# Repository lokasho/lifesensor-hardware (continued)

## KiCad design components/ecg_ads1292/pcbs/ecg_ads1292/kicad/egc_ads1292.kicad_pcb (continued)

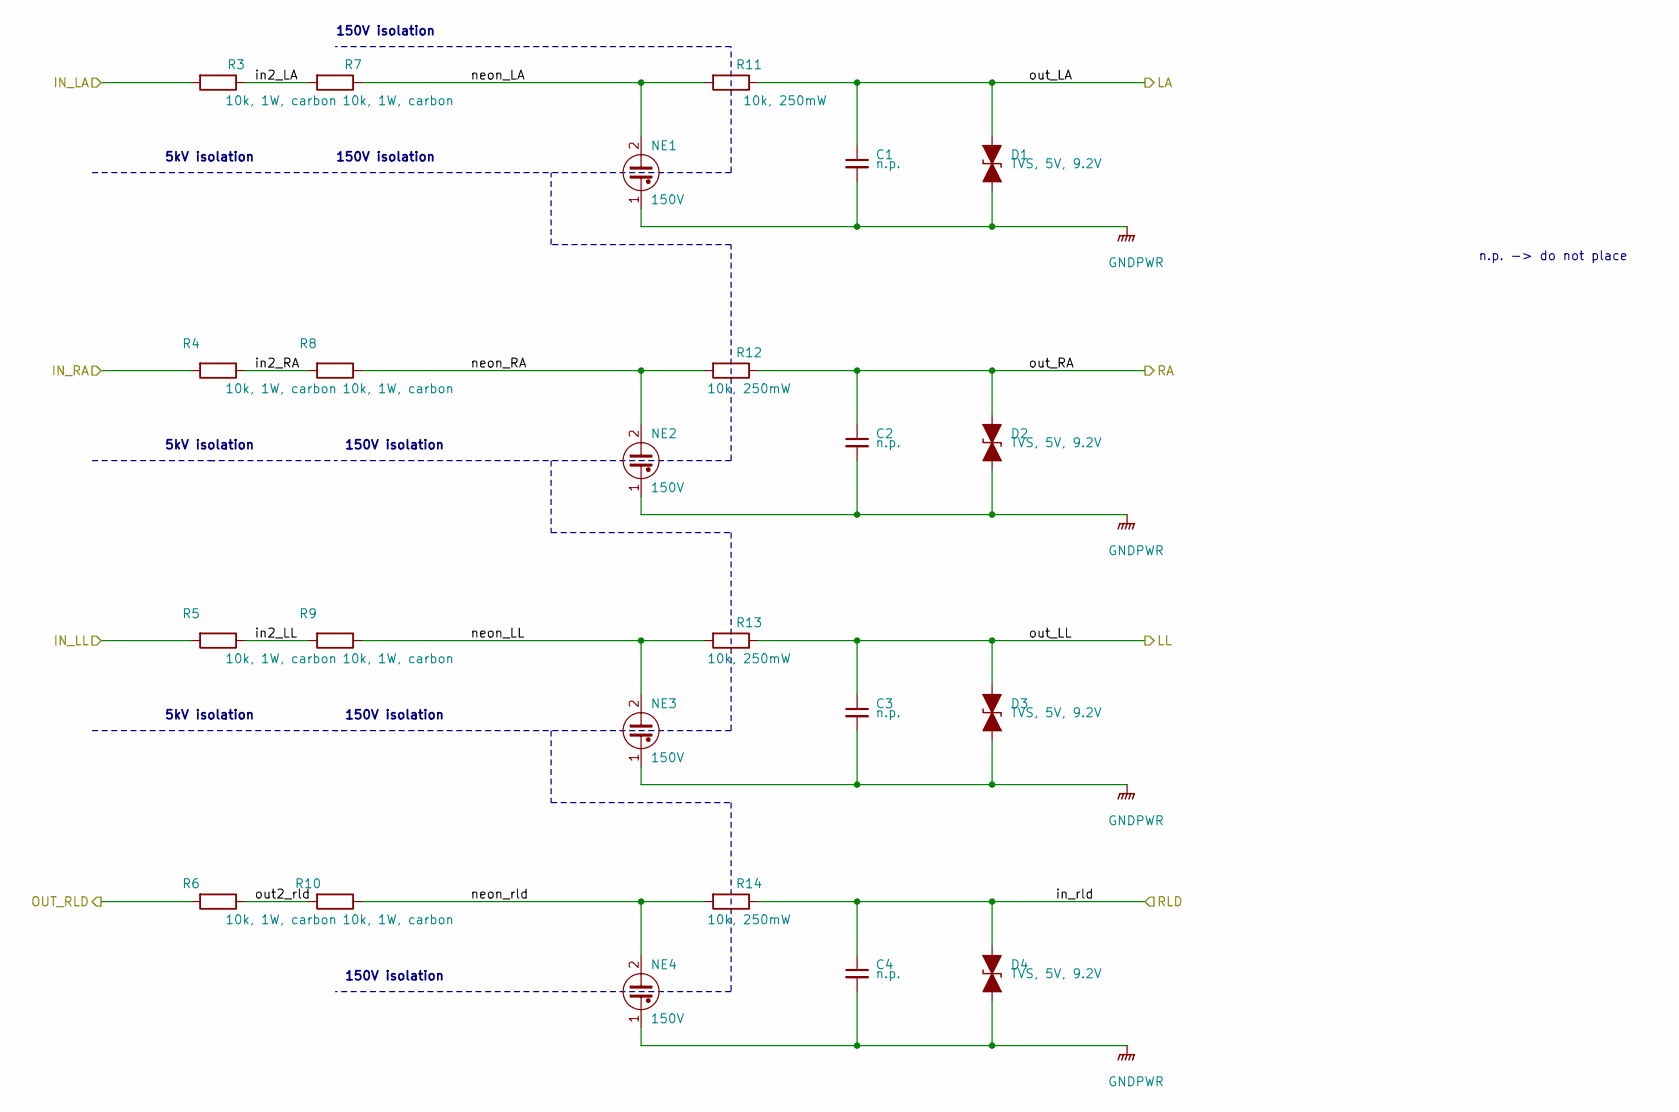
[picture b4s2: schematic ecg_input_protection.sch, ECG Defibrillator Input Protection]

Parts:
C1, C2, C3, C4: n.p.; C_Rect_L4.0mm_W2.5mm_P2.50mm
D1, D2, D3, D4: TVS, 5V, 9.2V; D_SMB_Handsoldering
NE1, NE2, NE3, NE4: 150V; C_Radial_D8.0mm_H11.5mm_P3.50mm
R3, R4, R5, R6, R7, R8, R9, R10: 10k, 1W, carbon; R_Axial_DIN0309_L9.0mm_D3.2mm_P12.70mm_Horizontal
R11, R12, R13, R14: 10k, 250mW; R_Axial_DIN0207_L6.3mm_D2.5mm_P10.16mm_Horizontal

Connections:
/ecg input protection/in2_LA: R3.1, R7.2
/ecg input protection/in2_LL: R5.1, R9.2
/ecg input protection/in2_RA: R4.1, R8.2
/ecg input protection/neon_LA: NE1.2, R7.1, R11.2
/ecg input protection/neon_LL: NE3.2, R9.1, R13.2
/ecg input protection/neon_RA: NE2.2, R8.1, R12.2
/ecg input protection/neon_rld: NE4.2, R10.1, R14.2
/ecg input protection/out2_rld: R6.1, R10.2
/in_LA: R3.2; also elsewhere on the board
/in_LL: R5.2; also elsewhere on the board
/in_RA: R4.2; also elsewhere on the board
/out_rld: R6.2; also elsewhere on the board
/protected_LA: C1.1, D1.1 (A1), R11.1; also elsewhere on the board
/protected_LL: C3.1, D3.1 (A1), R13.1; also elsewhere on the board
/protected_RA: C2.1, D2.1 (A1), R12.1; also elsewhere on the board
/protected_RLD: C4.1, D4.1 (A1), R14.1; also elsewhere on the board
GNDPWR: C1.2, C2.2, C3.2, C4.2, D1.2 (A2), D2.2 (A2), D3.2 (A2), D4.2 (A2), NE1.1, NE2.1, NE3.1, NE4.1; also elsewhere on the board

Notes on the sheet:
150V isolation
5kV isolation
n.p. -> do not place

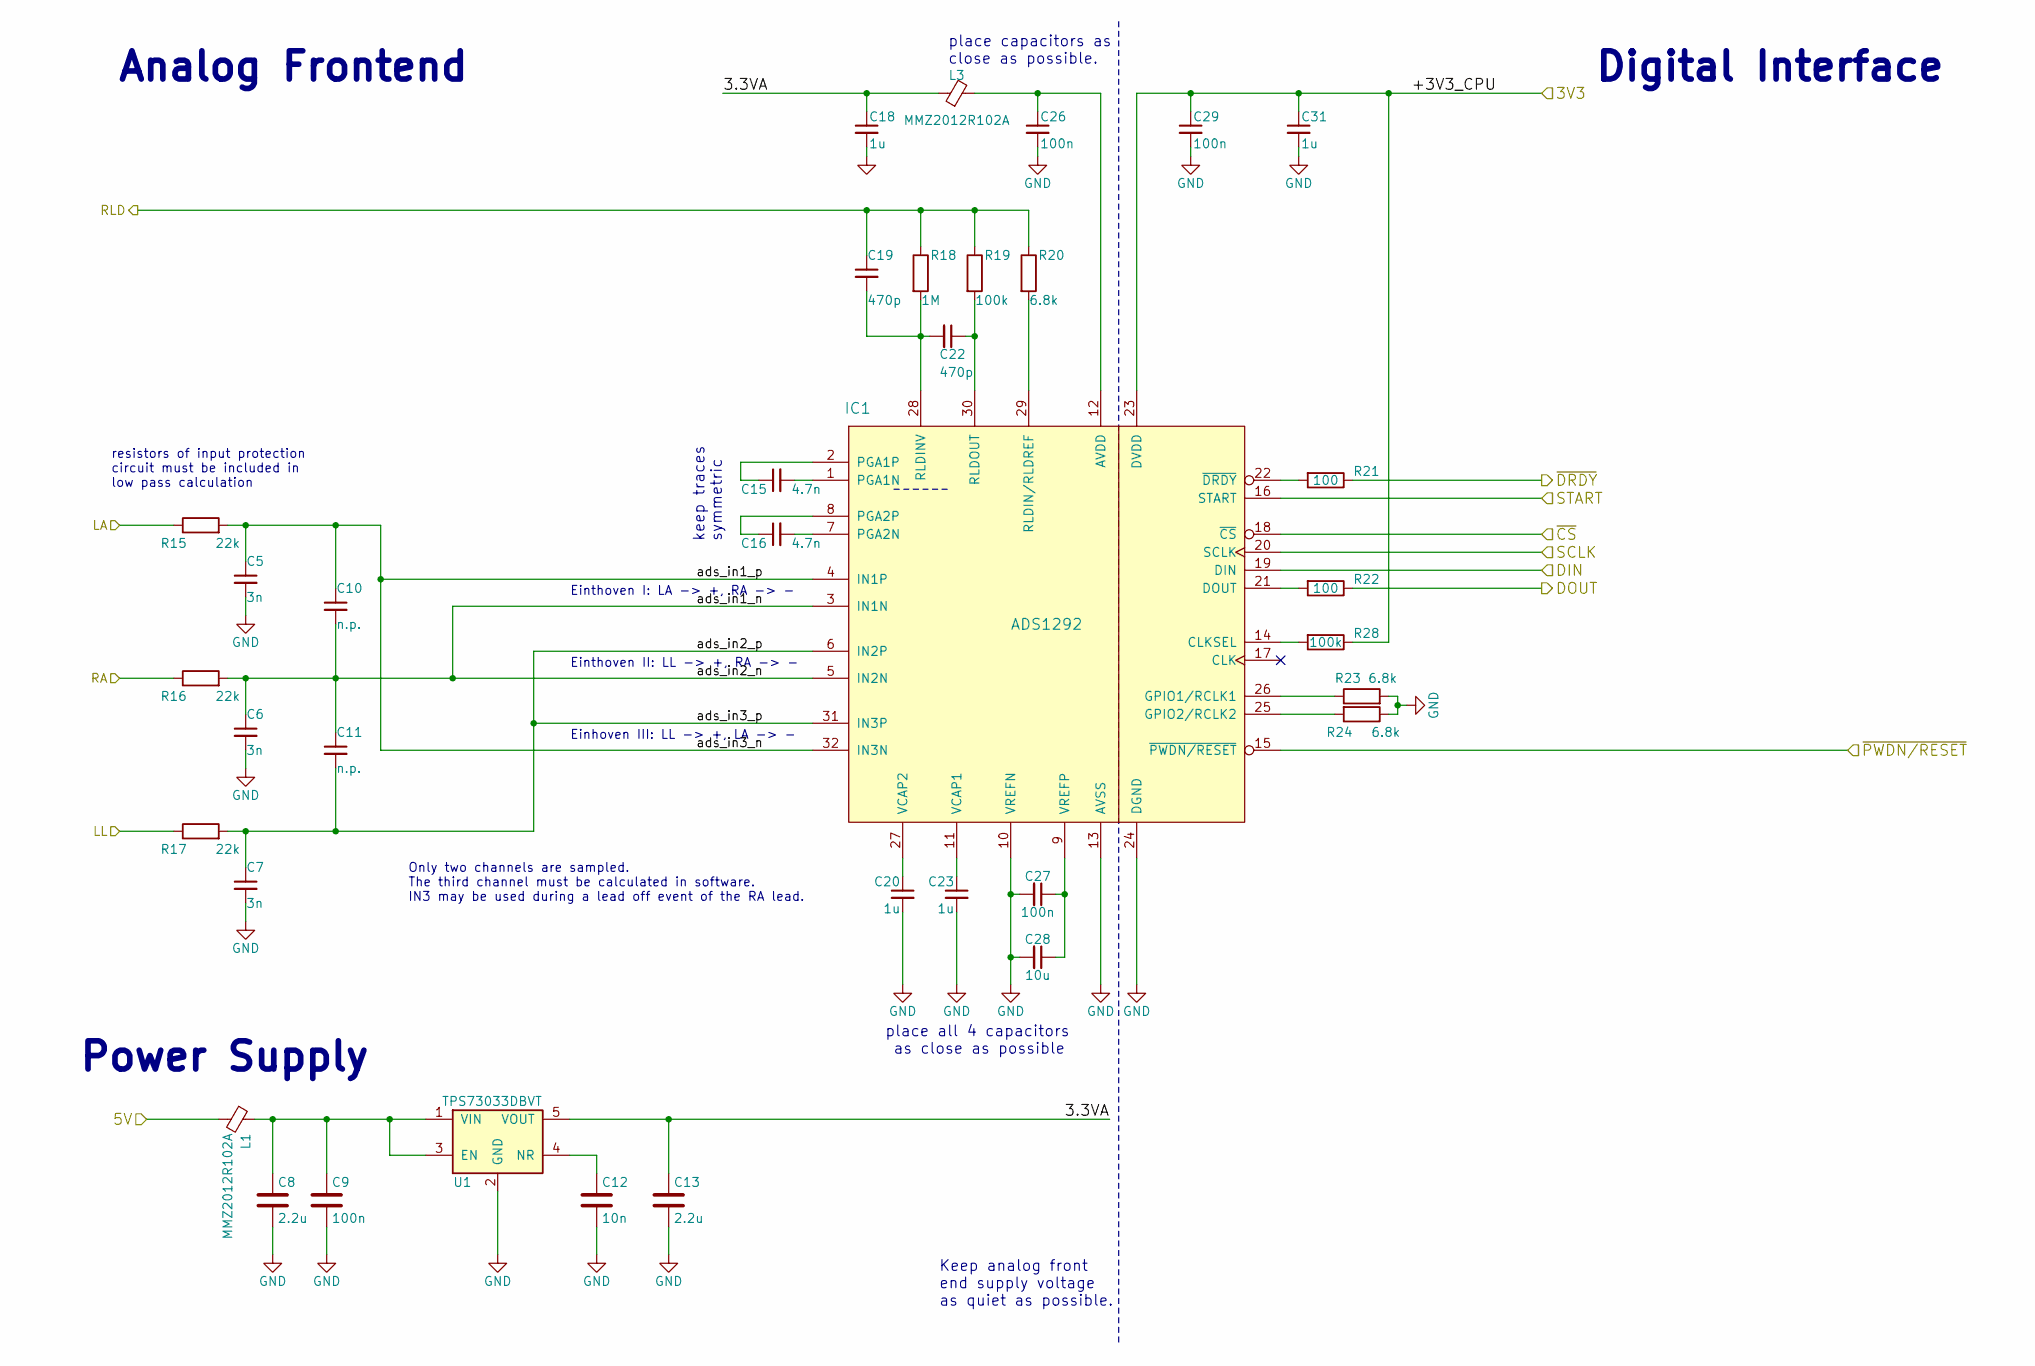
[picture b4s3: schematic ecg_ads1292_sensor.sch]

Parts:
C5, C6, C7: 3n; C_0603_1608Metric_Pad1.05x0.95mm_HandSolder; Farnell 1865491
C8, C13: 2.2u; C_0603_1608Metric_Pad1.05x0.95mm_HandSolder; Farnell 1797012
C9, C26, C29: 100n; C_0603_1608Metric_Pad1.05x0.95mm_HandSolder; Farnell 1907318
C10, C11: n.p.; C_0603_1608Metric_Pad1.05x0.95mm_HandSolder; Farnell 1865491
C12: 10n; C_0603_1608Metric_Pad1.05x0.95mm_HandSolder; Farnell 2496825
C15, C16: 4.7n; C_0603_1608Metric_Pad1.05x0.95mm_HandSolder; Farnell 2611918
C18, C20, C23, C31: 1u; C_0603_1608Metric_Pad1.05x0.95mm_HandSolder; Farnell 2112849
C19, C22: 470p; C_0603_1608Metric_Pad1.05x0.95mm_HandSolder
C27: 100n; C_0603_1608Metric_Pad1.05x0.95mm_HandSolder; Farnell 2494294
C28: 10u; C_0603_1608Metric_Pad1.05x0.95mm_HandSolder; Farnell 1889276
IC1: ADS1292; LQFP-32_5x5mm_P0.5mm
L1, L3: MMZ2012R102A; L_0805_2012Metric_Pad1.15x1.40mm_HandSolder; Farnell 1669719
R15, R16, R17: 22k; R_0603_1608Metric_Pad1.05x0.95mm_HandSolder; Farnell 1469825
R18: 1M; R_0603_1608Metric_Pad1.05x0.95mm_HandSolder; Farnell 1469746
R19: 100k; R_0603_1608Metric_Pad1.05x0.95mm_HandSolder; Farnell 1692517
R20, R23, R24: 6.8k; R_0603_1608Metric_Pad1.05x0.95mm_HandSolder; Farnell 1738916
R21, R22: 100; R_0603_1608Metric_Pad1.05x0.95mm_HandSolder; Farnell 1739145
R28: 100k; R_0603_1608Metric_Pad1.05x0.95mm_HandSolder; Farnell 1739145
U1: TPS73033DBVT; SOT-23-5_HandSoldering; Farnell 1135395

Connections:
/3V3: C29.1, C31.1, IC1.23 (DVDD), R28.1; also elsewhere on the board
/5V: L1.2; also elsewhere on the board
/ECG Sensor/3.3VA: C13.1, C18.1, L3.1, U1.5 (VOUT)
/ECG Sensor/ads_in1_n: C6.1, C10.2, C11.1, IC1.3 (IN1N), IC1.5 (IN2N), R16.2
/ECG Sensor/ads_in1_p: C5.1, C10.1, IC1.4 (IN1P), IC1.32 (IN3N), R15.2
/ECG Sensor/ads_in2_p: C7.1, C11.2, IC1.6 (IN2P), IC1.31 (IN3P), R17.2
/MISO: R22.1; also elsewhere on the board
/MOSI: IC1.19 (DIN); also elsewhere on the board
/SCLK: IC1.20 (SCLK); also elsewhere on the board
/START: IC1.16 (START); also elsewhere on the board
/protected_LA: R15.1; also elsewhere on the board
/protected_LL: R17.1; also elsewhere on the board
/protected_RA: R16.1; also elsewhere on the board
/protected_RLD: C19.1, R18.1, R19.1, R20.1; also elsewhere on the board
/~CS_ECG: IC1.18 (~CS); also elsewhere on the board
/~DRDY: R21.1; also elsewhere on the board
/~PDN_RESET: IC1.15 (~PWDN/RESET); also elsewhere on the board
GND: C5.2, C6.2, C7.2, C8.2, C9.2, C12.2, C13.2, C18.2, C20.2, C23.2, C26.2, C27.2, C28.2, C29.2, C31.2, IC1.10 (VREFN), IC1.13 (AVSS), IC1.24 (DGND), R23.2, R24.1, U1.2 (GND); also elsewhere on the board
unnamed: C8.1, C9.1, L1.1, U1.1 (VIN), U1.3 (EN)
unnamed: C12.1, U1.4 (NR)
unnamed: C15.1, IC1.2 (PGA1P)
unnamed: C15.2, IC1.1 (PGA1N)
unnamed: C16.1, IC1.8 (PGA2P)
unnamed: C16.2, IC1.7 (PGA2N)
unnamed: C19.2, C22.2, IC1.28 (RLDINV), R18.2
unnamed: C20.1, IC1.27 (VCAP2)
unnamed: C22.1, IC1.30 (RLDOUT), R19.2
unnamed: C23.1, IC1.11 (VCAP1)
unnamed: C26.1, IC1.12 (AVDD), L3.2
unnamed: C27.1, C28.1, IC1.9 (VREFP)
unnamed: IC1.14 (CLKSEL), R28.2
unnamed: IC1.21 (DOUT), R22.2
unnamed: IC1.22 (~DRDY), R21.2
unnamed: IC1.25 (GPIO2/RCLK2), R24.2
unnamed: IC1.26 (GPIO1/RCLK1), R23.1
unnamed: IC1.29 (RLDIN/RLDREF), R20.2

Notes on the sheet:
place all 4 capacitors as close as possible
Digital Interface
Analog Frontend
Keep analog front end supply voltage as quiet as possible.
place capacitors as close as possible.
keep traces symmetric
Power Supply
Einthoven I: LA -> +, RA -> -
Einthoven II: LL -> +, RA -> -
Einhoven III: LL -> +, LA -> -
resistors of input protection circuit must be included in low pass calculation
Only two channels are sampled. The third channel must be calculated in software. IN3 may be used during a lead off event of the RA lead.

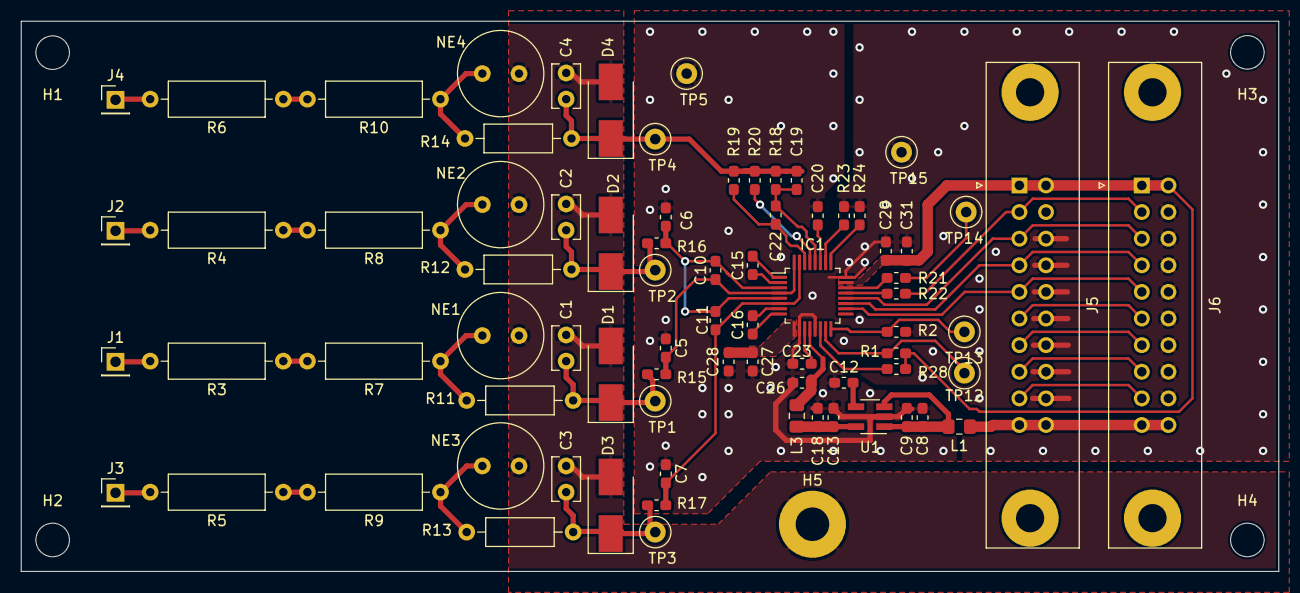
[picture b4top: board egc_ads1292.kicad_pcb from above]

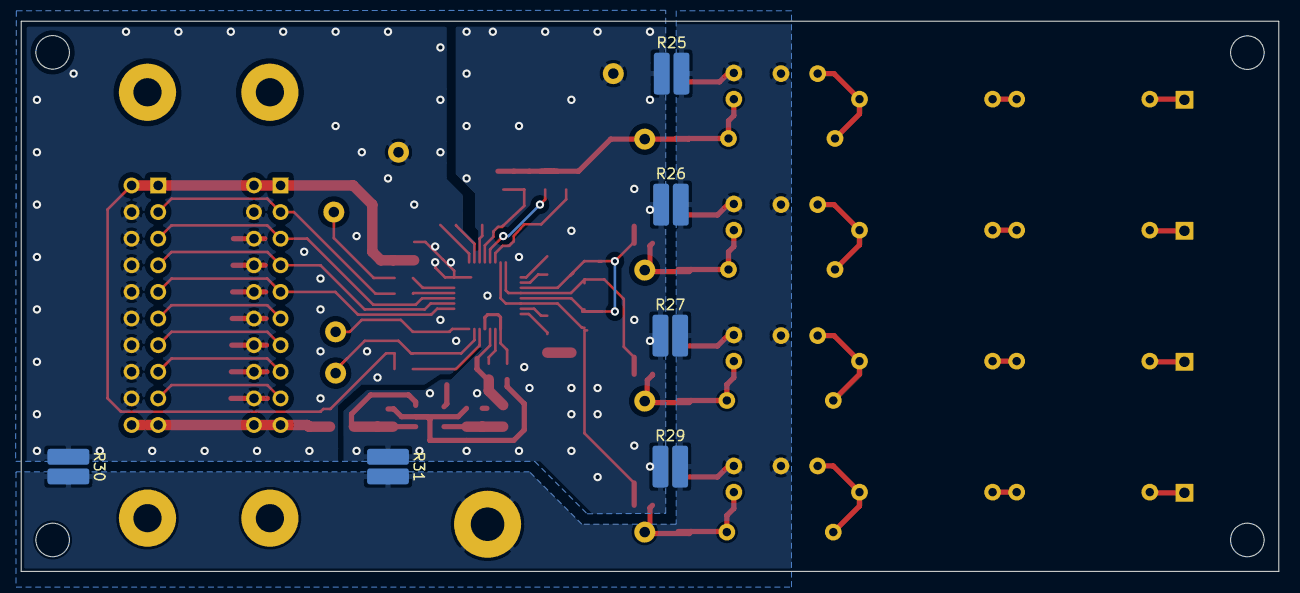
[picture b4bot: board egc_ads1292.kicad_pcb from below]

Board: 2 copper layers, 120.0 x 52.5 mm, 88 parts (6 on the bottom side), 53 nets.

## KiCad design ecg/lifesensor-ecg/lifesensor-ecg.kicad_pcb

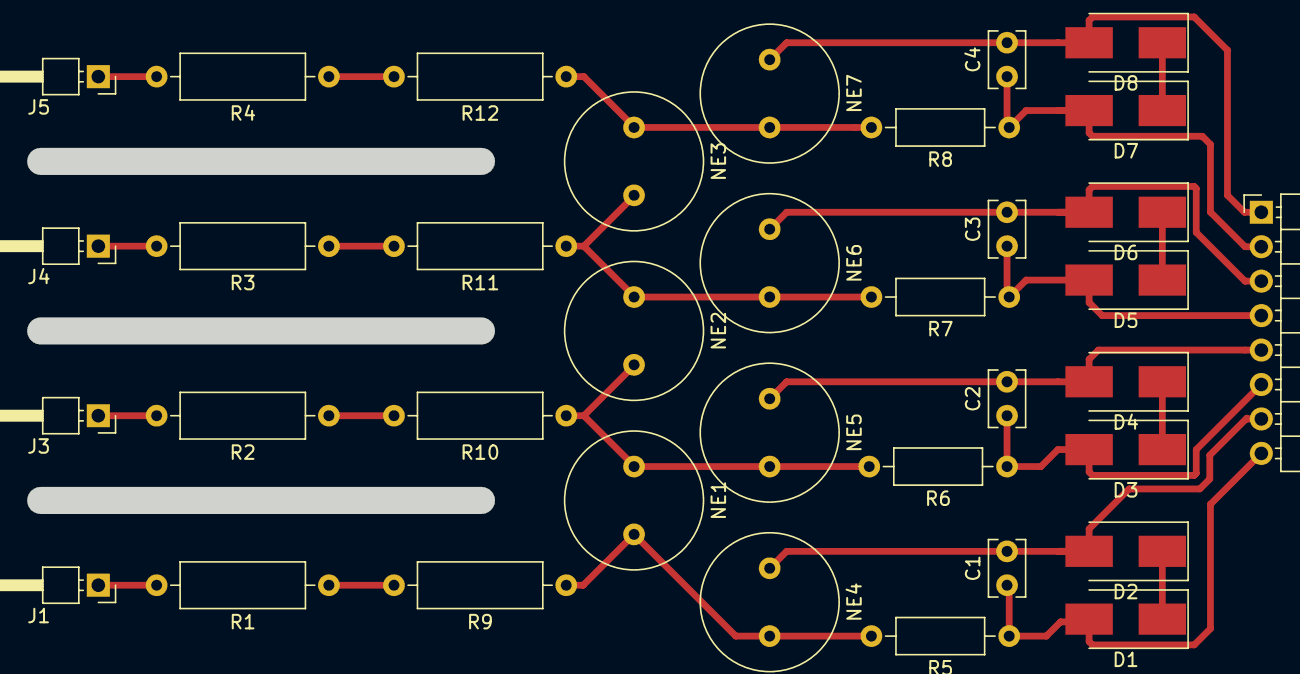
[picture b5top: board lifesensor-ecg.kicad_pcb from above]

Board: 2 copper layers, 36 parts (0 on the bottom side), 24 nets.

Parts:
C1, C2, C3, C4: C_Small; C_Rect_L4.0mm_W2.5mm_P2.50mm
D1, D2, D3, D4, D5, D6, D7, D8: D_Zener_ALT; D_SMB_Handsoldering
J1, J3, J4, J5: Conn_01x01_Female; PinHeader_1x01_P2.54mm_Horizontal
J2: Conn_01x08_Female; PinHeader_1x08_P2.54mm_Horizontal
NE1, NE2, NE3, NE4, NE5, NE6, NE7: 150V; C_Radial_D10.0mm_H12.5mm_P5.00mm
R1, R2, R3, R4, R9, R10, R11, R12: 10k, 1W, carbon; R_Axial_DIN0309_L9.0mm_D3.2mm_P12.70mm_Horizontal
R5: 10k, 250mW; R_Axial_DIN0207_L6.3mm_D2.5mm_P10.16mm_Horizontal
R6, R7, R8: R; R_Axial_DIN0207_L6.3mm_D2.5mm_P10.16mm_Horizontal

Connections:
/ecg_input_protection/gn_ch1: C1.2, D2.2, J2.7, NE4.1
/ecg_input_protection/gnd_ch2: C2.2, D4.2, J2.5, NE5.1
/ecg_input_protection/gnd_ch3: C3.2, D6.2, J2.3, NE6.1
/ecg_input_protection/gnd_rld: C4.2, D8.2, J2.1, NE7.1
/ecg_input_protection/in_ch1: J1.1, R1.2
/ecg_input_protection/in_ch2: J3.1, R2.2
/ecg_input_protection/in_ch3: J4.1, R3.2
/ecg_input_protection/in_rld: C4.1, D7.2, J2.2, R8.1
/ecg_input_protection/neon_ch1: NE1.2, NE4.2, R5.2, R9.1
/ecg_input_protection/neon_ch2: NE1.1, NE2.2, NE5.2, R6.2, R10.1
/ecg_input_protection/neon_ch3: NE2.1, NE3.2, NE6.2, R7.2, R11.1
/ecg_input_protection/neon_rld: NE3.1, NE7.2, R8.2, R12.1
/ecg_input_protection/out_ch1: C1.1, D1.2, J2.8, R5.1
/ecg_input_protection/out_ch2: C2.1, D3.2, J2.6, R6.1
/ecg_input_protection/out_ch3: C3.1, D5.2, J2.4, R7.1
/ecg_input_protection/out_rld: J5.1, R4.2
unnamed: D1.1, D2.1
unnamed: D3.1, D4.1
unnamed: D5.1, D6.1
unnamed: D7.1, D8.1
unnamed: R1.1, R9.2
unnamed: R2.1, R10.2
unnamed: R3.1, R11.2
unnamed: R4.1, R12.2

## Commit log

2020-03-26 add zenit resources
2020-03-27 update requirements
2020-03-27 add kicad project for ecg
2020-03-28 first draft ecg protection
2020-04-03 update file structure
2020-04-03 include analog frontend
2020-04-03 remove old ecg version
2020-04-03 add dummy ads1292 driver
2020-04-03 add dummy script
2020-04-07 update schematics
2020-04-11 allow daisy chaining and improve ground planes
2020-04-11 fix GND via not connected
2020-04-11 simplify ads1292 supply scheme in schematic
2020-04-15 orientation of pin headers in schematic matches pcb
2020-04-15 add gnd/gndpwr bridge at analog power supply
2020-04-15 add ERC log with allowed warnings
2020-04-15 add board name and version to pcb
2020-04-15 add version and titles to schematic pages
2020-04-22 first sim test with ne2 lib, blanks in sheet name removed
2020-04-25 updates simulation, adds diode, updates voltage source
2020-04-25 add system overview and pcb stack dimensions
2020-04-26 add templates for components and pcbs
2020-04-26 remove obsolete files
2020-04-26 allow scripts to be run from another working dir
2020-04-26 ignore python cache directories
2020-04-27 adds new tvs diode spice models
2020-04-27 new ecg_ads1292 version based on template
2020-04-27 update diode modell
2020-04-27 schematic passes erc with two accpted warnings
2020-04-27 schematic passes checklist
2020-04-27 the layout passes the checklist
2020-04-27 update check lists
2020-04-27 add gerber files
2020-04-27 add board svg image
2020-04-28 ignore schematic library cache in pcb template
2020-04-28 add chip select mux in pcb template
2020-04-28 add chip select mux in ads1292_main schematics
2020-04-28 add chip select mux on ads1292_main pcb
2020-04-28 update schematic check list
2020-04-29 fix project templates in pcb checklist
2020-04-29 better parameter name for lower_case_string function parameter
2020-05-07 add defiprotect_gdt component
2020-05-07 ecg_ads1292: fix symbol library paths
2020-05-07 add teardrops to layout
2020-05-07 ecg_ads1292 improve input filter circuit
2020-05-07 ecg_ads1292: improve power supply ferrit bead layout
2020-05-07 ecg_ads1292: remove obsolete pcb directory
2020-05-29 ecg_ads1292: update part fields
2020-05-31 ecg_ads1292: update schematic date
2020-05-31 ecg_ads1292: schematic checklist ok
2020-05-31 ecg_ads1292: layout checklist passed
2020-06-06 [WIP] ecg_ads1292: improve docs
2020-06-14 include board view svg instead of png in ads1292 README
2020-06-14 update parts and add digikey PNs
2020-06-14 add interactive BOM
2020-06-14 update parts in pcb
2020-06-18 add interconnect description
2020-06-18 update system overview
2020-06-20 remove outdated system overview png
2020-07-04 add ecg ads1292 pin/signal description to docs
2020-07-04 [WIP] adapt https://github.com/MitjaNemec/Kicad_action_plugins/blob/master/archive_project/archive_project.py
2020-07-07 move templates into common subdirectory
2020-07-07 use builtin __debug__ variable
2020-07-07 remove not used function parameters
2020-07-19 allow python version below 3.7
2020-07-19 remove old archive script
2020-07-19 add script to archive schematic symbols
2020-07-25 archive all components
2020-07-25 update docs
2020-08-25 add some tests
2020-08-25 improve pcb template
2020-08-25 board name defaults to None when creating a Settings object using python version below 3.7
2020-08-25 improve schematic check list
2020-08-25 create new component esp32_devkitc
2020-08-25 Add ESP32 DevKit-C symbol and footprint from snap eda
2020-08-25 add devkitc to board
2020-08-26 improve docs markdown templates
2020-08-26 ignore kicad symbol cache files
2020-08-26 adapt ecg_ads1292 docs to the template changes
2020-10-13 clean python scripts structure
2020-10-13 update interconnect
2020-10-13 add ESP32, WROOM32, DEVKIT-C data sheets
2020-10-13 [WIP] develop ESP32-main pcb
2020-10-13 add system overview to esp32 docs
2020-10-13 sackgasse1
2020-10-13 updates temp
2020-10-13 adds TODOs
2020-11-01 updates TODOs
2020-11-01 adds pinout table for devkitc
2020-11-01 updates pinout of esp32 devkitc, adds pinout odt document
2020-11-13 first drafted routing, WARNING: JTAG TCK missing!
2020-11-14 adds todos and notes
2020-11-22 Ready for review! fixes JTAG, adds updated pinout, updates JTAG header docu in Development_esp32_devkitc, finishes routing, adds JTAG resistors according to ESP32 manual
2020-11-24 small cleanup
2020-12-01 minorthing
2020-12-01 small update
2020-12-01 moves R21 below devkit
2020-12-01 Move FB1 closer to interconnect
2020-12-01 removes filling
2020-12-01 remove fillings for merge
2020-12-05 adds gpio expander, WIP
2020-12-05 updates 5V jack, adds jumpers for I2C GPIO Expander Adress, updates pinout, updates docs
2020-12-08 improve GND return paths for display SPI signals
